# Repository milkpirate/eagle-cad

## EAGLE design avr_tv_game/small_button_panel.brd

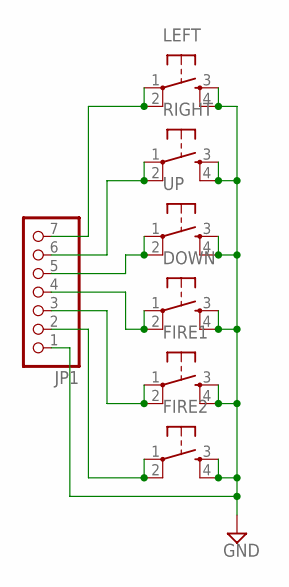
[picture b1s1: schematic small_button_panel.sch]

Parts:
DOWN: TAC_SWITCHPTH; TACTILE-PTH
FIRE1, FIRE2: TAC_SWITCHPTH; TACTILE-PTH
JP1: PINHD-1X7; 1X07
LEFT: TAC_SWITCHPTH; TACTILE-PTH
RIGHT: TAC_SWITCHPTH; TACTILE-PTH
UP: TAC_SWITCHPTH; TACTILE-PTH

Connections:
GND: DOWN.3, DOWN.4, FIRE1.3, FIRE1.4, FIRE2.3, FIRE2.4, JP1.1, LEFT.3, LEFT.4, RIGHT.3, RIGHT.4, UP.3, UP.4
unnamed: JP1.7, LEFT.1, LEFT.2
unnamed: JP1.5, UP.1, UP.2
unnamed: FIRE2.1, FIRE2.2, JP1.2
unnamed: FIRE1.1, FIRE1.2, JP1.3
unnamed: DOWN.1, DOWN.2, JP1.4
RIGHT: JP1.6, RIGHT.1, RIGHT.2

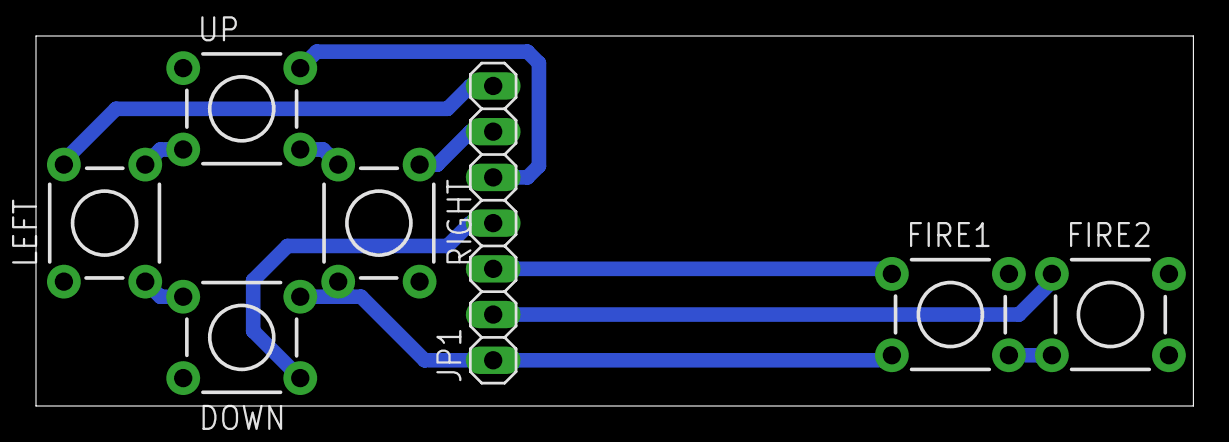
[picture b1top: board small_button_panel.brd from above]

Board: 2 copper layers, 64.3 x 20.6 mm, 7 parts (0 on the bottom side), 7 nets.

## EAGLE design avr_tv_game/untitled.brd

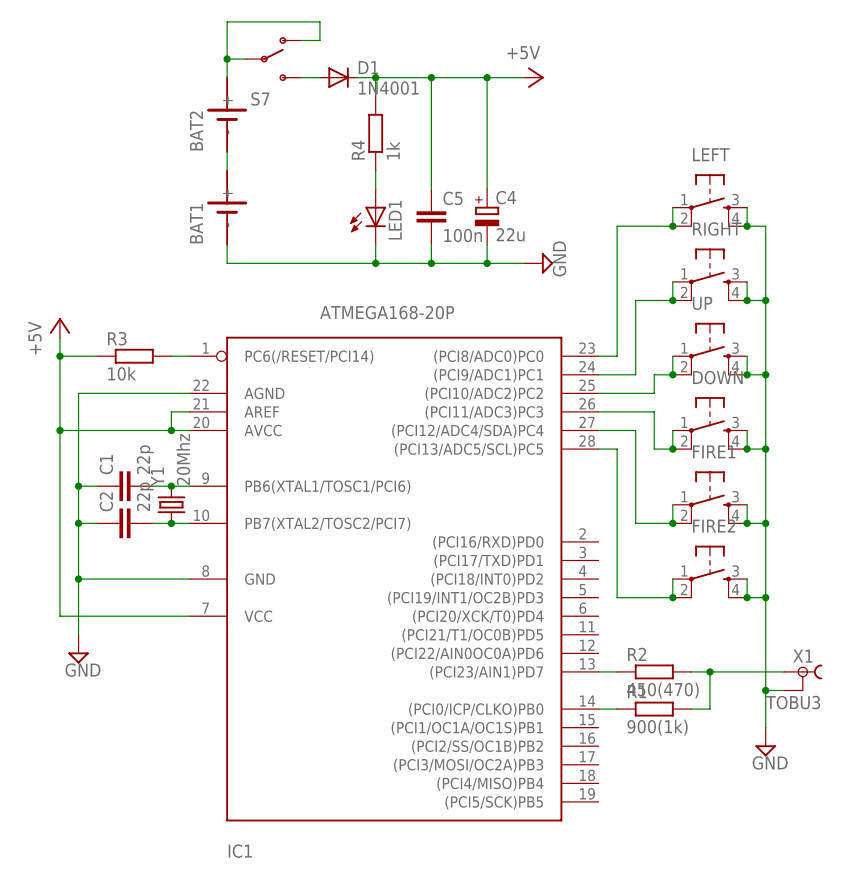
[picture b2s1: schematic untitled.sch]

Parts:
BAT1, BAT2: SN2032
C1, C2: 22p; C025-025X050
C4: 22u; TT2D5L
C5: 100n; C025-025X050
D1: 1N4001; D-2.5
DOWN: TAC_SWITCHPTH; TACTILE-PTH
FIRE1, FIRE2: TAC_SWITCHPTH; TACTILE-PTH
IC1: ATMEGA168-20P; DIL28-3
LED1: LED3MM
LEFT: TAC_SWITCHPTH; TACTILE-PTH
R1: 900(1k); 0207/2V
R2: 450(470); 0207/2V
R3: 10k; 0207/10
R4: 1k; 0204V
RIGHT: TAC_SWITCHPTH; TACTILE-PTH
S7: SWITCH-SPSTPTH; SWITCH-SPDT
UP: TAC_SWITCHPTH; TACTILE-PTH
X1: TOBU3
Y1: 20Mhz; HC49US

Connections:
+5V: C4.+, C5.1, D1.C, IC1.7 (VCC), IC1.20 (AVCC), IC1.21 (AREF), R3.1, R4.2
GND: BAT1.-, C1.1, C2.1, C4.-, C5.2, DOWN.3, DOWN.4, FIRE1.3, FIRE1.4, FIRE2.3, FIRE2.4, IC1.8 (GND), IC1.22 (AGND), LED1.K (C), LEFT.3, LEFT.4, RIGHT.3, RIGHT.4, UP.3, UP.4, X1.2, X1.2@1 (2), X1.2@2 (2)
unnamed: C1.2, IC1.9 (PB6(XTAL1/TOSC1/PCI6)), Y1.2
unnamed: C2.2, IC1.10 (PB7(XTAL2/TOSC2/PCI7)), Y1.1
unnamed: BAT2.+, S7.1 (O), S7.2
unnamed: IC1.23 ((PCI8/ADC0)PC0), LEFT.1, LEFT.2
unnamed: LED1.A, R4.1
unnamed: IC1.25 ((PCI10/ADC2)PC2), UP.1, UP.2
unnamed: IC1.1 (PC6(/RESET/PCI14)), R3.2
unnamed: FIRE2.1, FIRE2.2, IC1.28 ((PCI13/ADC5/SCL)PC5)
unnamed: FIRE1.1, FIRE1.2, IC1.27 ((PCI12/ADC4/SDA)PC4)
unnamed: DOWN.1, DOWN.2, IC1.26 ((PCI11/ADC3)PC3)
unnamed: D1.A, S7.3 (S)
unnamed: BAT1.+, BAT2.-
unnamed: IC1.14 ((PCI0/ICP/CLKO)PB0), R1.1
unnamed: IC1.13 ((PCI23/AIN1)PD7), R2.1
unnamed: R1.2, R2.2, X1.1
RIGHT: IC1.24 ((PCI9/ADC1)PC1), RIGHT.1, RIGHT.2

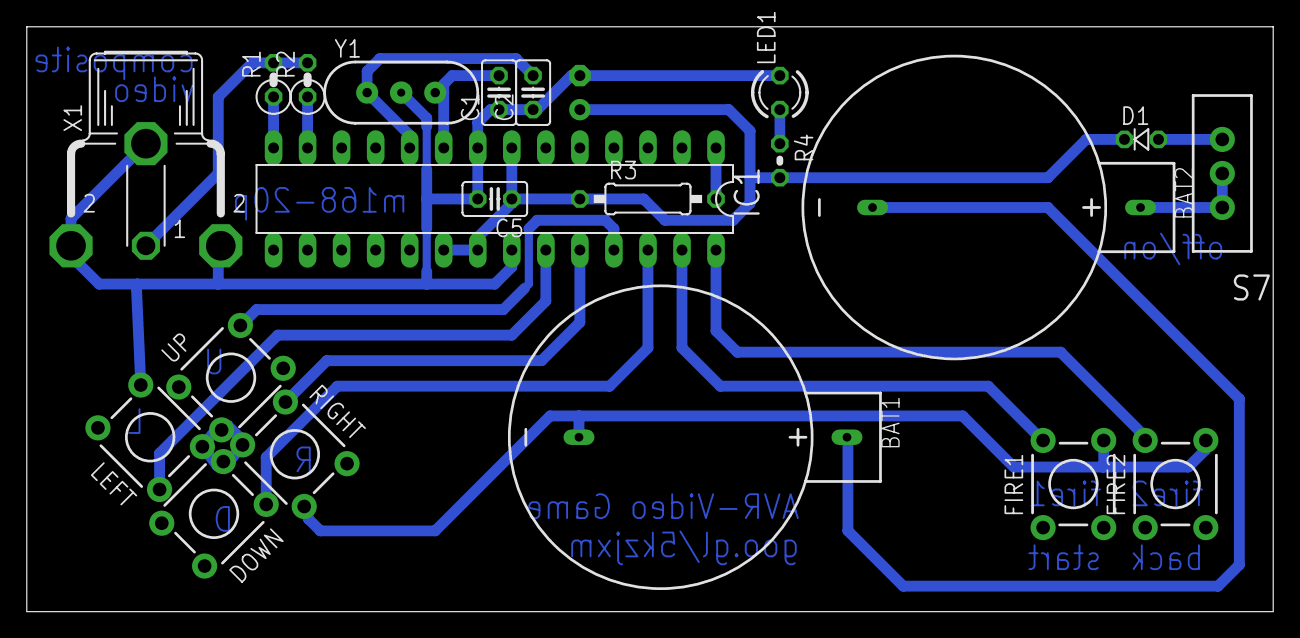
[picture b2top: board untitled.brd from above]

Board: 2 copper layers, 93.0 x 43.6 mm, 22 parts (1 on the bottom side), 18 nets.

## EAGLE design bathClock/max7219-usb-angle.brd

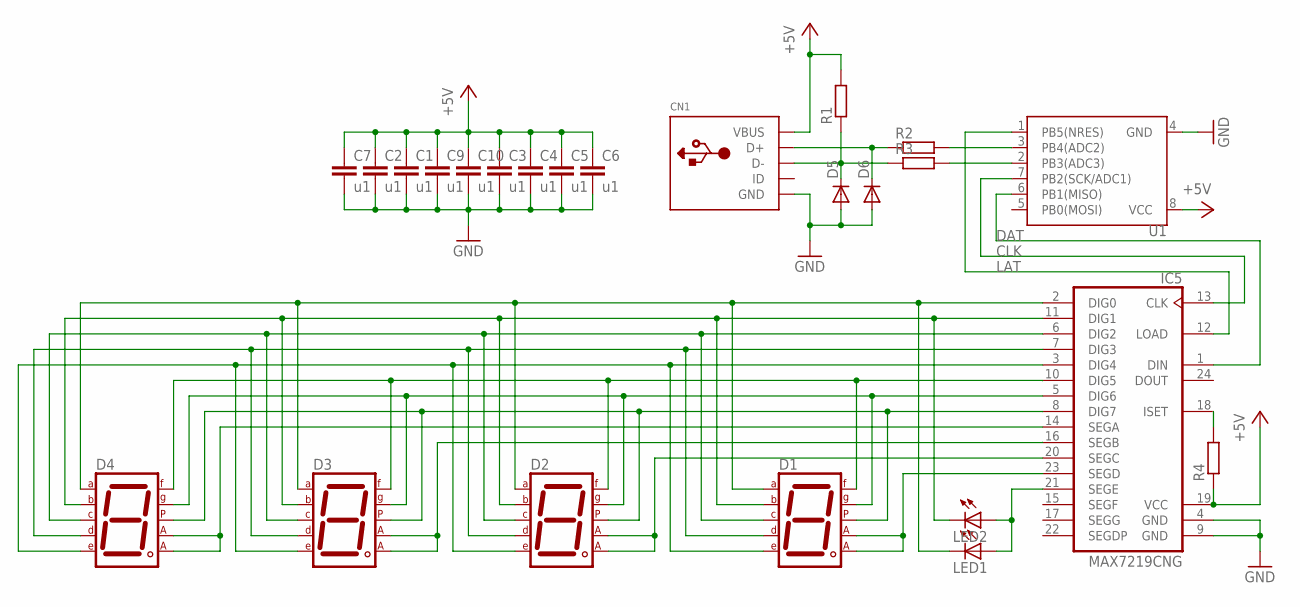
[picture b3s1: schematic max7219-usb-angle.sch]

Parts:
C1, C2, C3, C4, C5, C6, C7, C9, C10: u1; C0805K
CN1: USBTHM; USB-MINIB-THM
D1, D2, D3, D4: 7SEG-CA; 7SEG-13
D5, D6: DIODE-MINIMELF; MINIMELF
IC5: MAX7219CNG; DIL24-3
LED1, LED2: LED3MM
R1, R2, R3: R-EU_M0805; M0805
R4: R-EU_R0805; R0805
U1: ATTINY45ATTINYX5-20-DIP-GAP; DIL08

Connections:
+5V: C1.1, C2.1, C3.1, C4.1, C5.1, C6.1, C7.1, C9.1, C10.1, CN1.VBUS, IC5.19 (VCC), R1.2, R4.1, U1.8 (VCC)
CLK: IC5.13 (CLK), U1.7 (PB2(SCK/ADC1))
DAT: IC5.1 (DIN), U1.6 (PB1(MISO))
GND: C1.2, C2.2, C3.2, C4.2, C5.2, C6.2, C7.2, C9.2, C10.2, CN1.GND, D5.A, D6.A, IC5.4 (GND), IC5.9 (GND), U1.4 (GND)
LAT: IC5.12 (LOAD), U1.1 (PB5(NRES))
unnamed: D2.3 (CA1), D2.8 (CA2), IC5.20 (SEGC)
unnamed: D4.3 (CA1), D4.8 (CA2), IC5.14 (SEGA)
unnamed: D1.3 (CA1), D1.8 (CA2), IC5.23 (SEGD)
unnamed: IC5.21 (SEGE), LED1.A, LED2.A
unnamed: D1.7 (A), D2.7 (A), D3.7 (A), D4.7 (A), IC5.2 (DIG0), LED1.K (C)
unnamed: D1.6 (B), D2.6 (B), D3.6 (B), D4.6 (B), IC5.11 (DIG1), LED2.K (C)
unnamed: D1.4 (C), D2.4 (C), D3.4 (C), D4.4 (C), IC5.6 (DIG2)
unnamed: D1.2 (D), D2.2 (D), D3.2 (D), D4.2 (D), IC5.7 (DIG3)
unnamed: D1.1 (E), D2.1 (E), D3.1 (E), D4.1 (E), IC5.3 (DIG4)
unnamed: D1.9 (F), D2.9 (F), D3.9 (F), D4.9 (F), IC5.10 (DIG5)
unnamed: D1.10 (G), D2.10 (G), D3.10 (G), D4.10 (G), IC5.5 (DIG6)
unnamed: D1.5 (DP), D2.5 (DP), D3.5 (DP), D4.5 (DP), IC5.8 (DIG7)
unnamed: IC5.18 (ISET), R4.2
unnamed: D3.3 (CA1), D3.8 (CA2), IC5.16 (SEGB)
unnamed: R2.2, U1.3 (PB4(ADC2))
unnamed: CN1.D-, D5.C, R1.1, R3.1
unnamed: CN1.D+, D6.C, R2.1
unnamed: R3.2, U1.2 (PB3(ADC3))

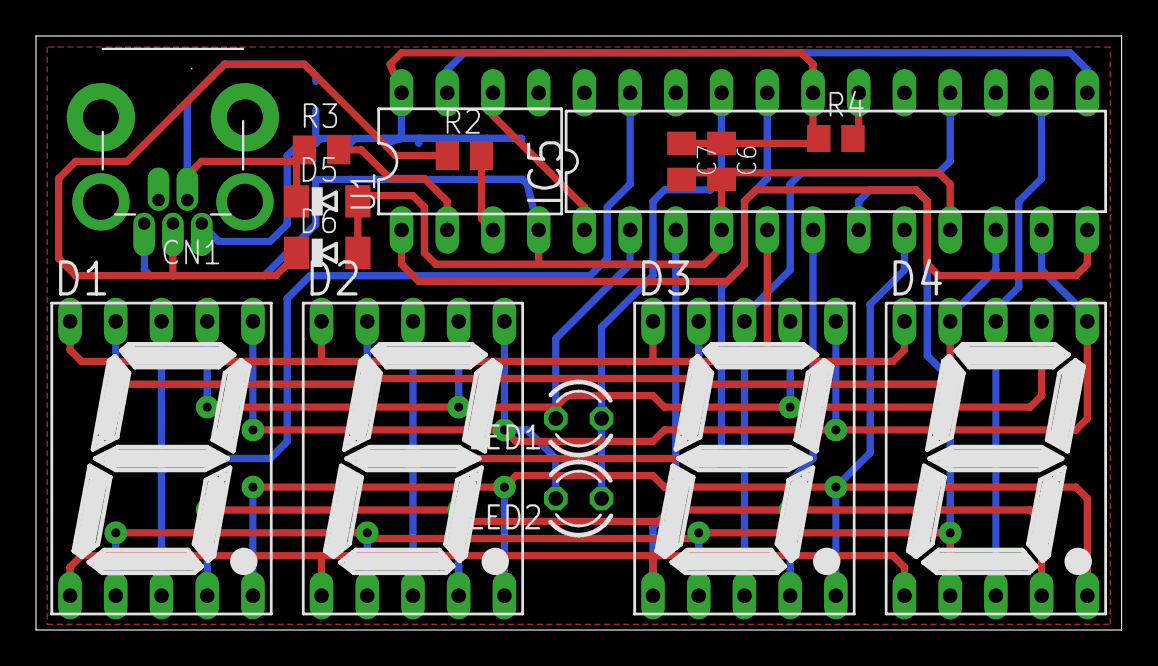
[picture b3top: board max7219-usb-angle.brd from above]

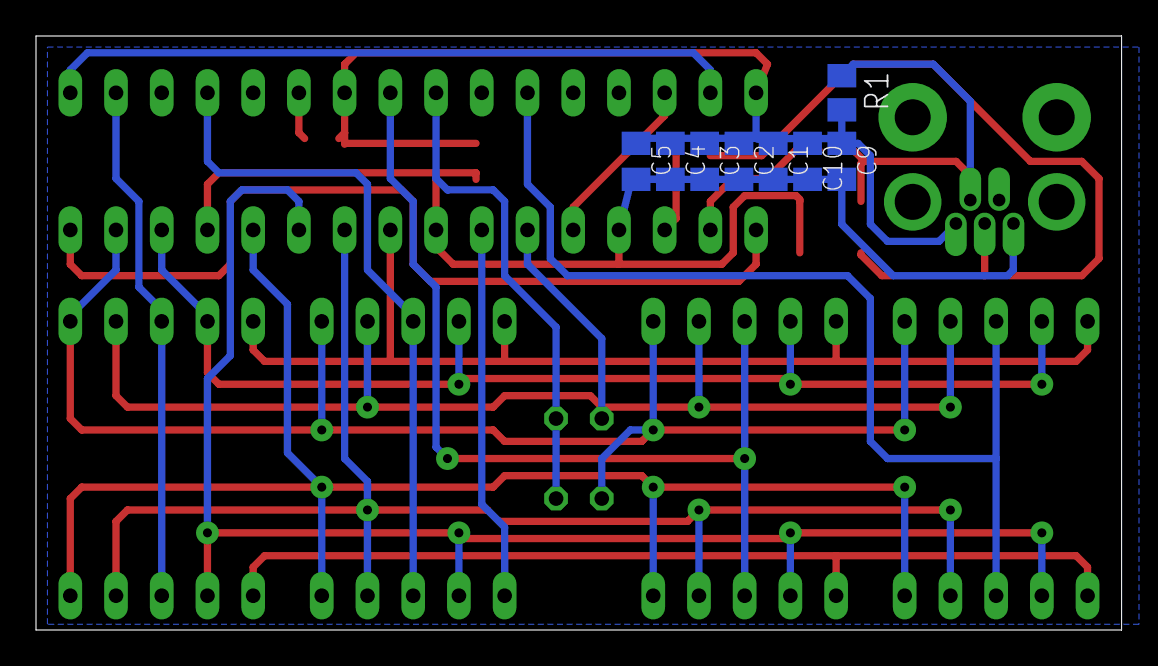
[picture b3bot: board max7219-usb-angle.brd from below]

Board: 2 copper layers, 60.3 x 33.0 mm, 24 parts (8 on the bottom side), 23 nets.

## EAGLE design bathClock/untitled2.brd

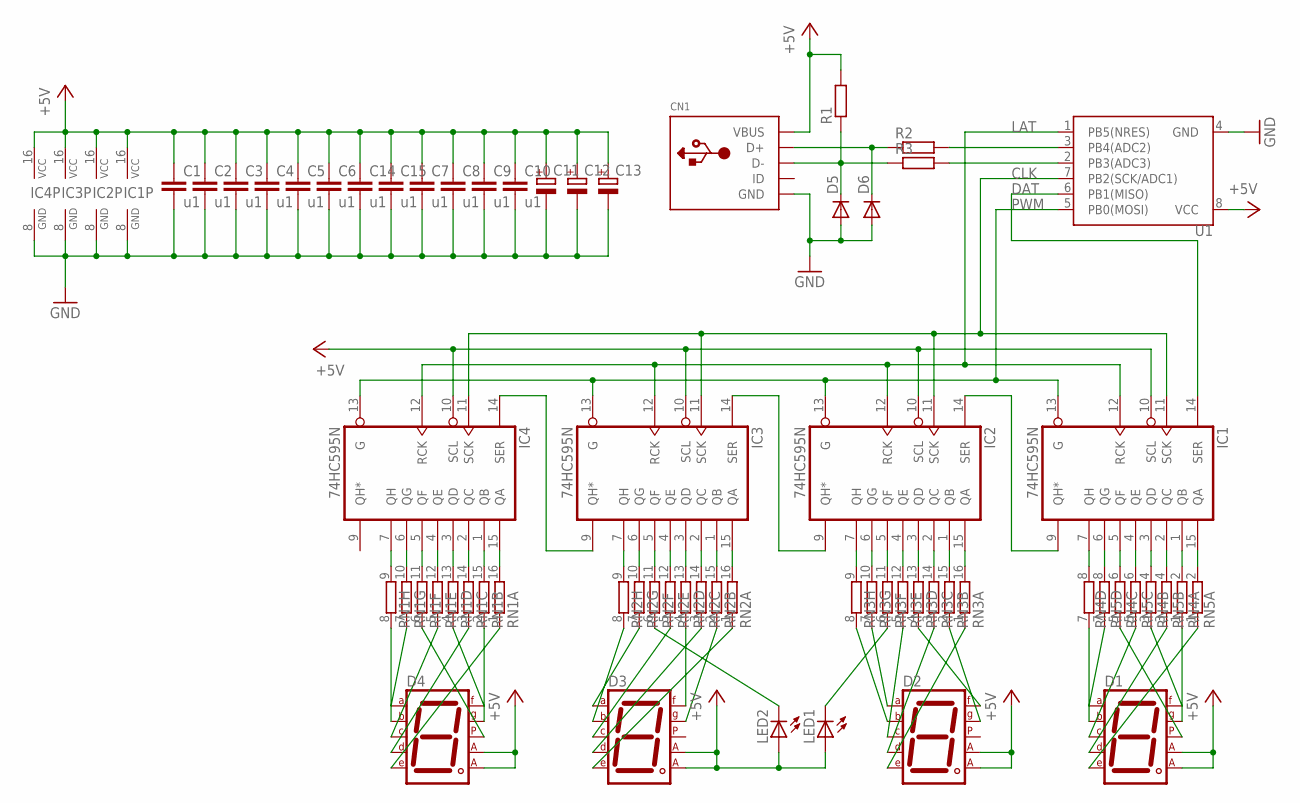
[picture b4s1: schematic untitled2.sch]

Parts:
C1, C2, C3, C4, C5, C6, C14, C15: u1; C025-025X050
C7, C8, C9, C10: u1; C0805K
C11: CPOL-EUE1.8-4; E1,8-4
C12, C13: CPOL-EUE2.5-7; E2,5-7
CN1: USBTHM; USB-MINIB-THM
D1, D2, D3, D4: 7SEG-CA; 7SEG-13
D5, D6: DIODE-D-7.5; D-7.5
IC1, IC2, IC3, IC4: 74HC595N; DIL16
LED1, LED2: LED3MM
R1, R2, R3: R-EU_0204/7; 0204/7
RN1, RN2, RN3: 8R-N; DIL16
RN4, RN5: E4R; SIL8
U1: ATTINY45ATTINYX5-20-DIP-GAP; DIL08

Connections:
+5V: C1.1, C2.1, C3.1, C4.1, C5.1, C6.1, C7.1, C8.1, C9.1, C10.1, C11.+, C12.+, C13.+, C14.1, C15.1, CN1.VBUS, D1.3 (CA1), D1.8 (CA2), D2.3 (CA1), D2.8 (CA2), D3.3 (CA1), D3.8 (CA2), D4.3 (CA1), D4.8 (CA2), IC1.10 (SCL), IC1.16 (VCC), IC2.10 (SCL), IC2.16 (VCC), IC3.10 (SCL), IC3.16 (VCC), IC4.10 (SCL), IC4.16 (VCC), LED1.A, LED2.A, R1.2, U1.8 (VCC)
CLK: IC1.11 (SCK), IC2.11 (SCK), IC3.11 (SCK), IC4.11 (SCK), U1.7 (PB2(SCK/ADC1))
DAT: IC1.14 (SER), U1.6 (PB1(MISO))
GND: C1.2, C2.2, C3.2, C4.2, C5.2, C6.2, C7.2, C8.2, C9.2, C10.2, C11.-, C12.-, C13.-, C14.2, C15.2, CN1.GND, D5.A, D6.A, IC1.8 (GND), IC2.8 (GND), IC3.8 (GND), IC4.8 (GND), U1.4 (GND)
LAT: IC1.12 (RCK), IC2.12 (RCK), IC3.12 (RCK), IC4.12 (RCK), U1.1 (PB5(NRES))
unnamed: D1.7 (A), RN5.7 (1)
unnamed: D1.6 (B), RN4.7 (1)
unnamed: D1.5 (DP), RN4.5 (1)
unnamed: D1.4 (C), RN5.5 (1)
unnamed: D1.9 (F), RN4.3 (1)
unnamed: D1.2 (D), RN5.3 (1)
unnamed: D1.10 (G), RN4.1
unnamed: D1.1 (E), RN5.1
unnamed: D4.9 (F), RN1.4 (1)
unnamed: D2.1 (E), RN3.1
unnamed: D2.2 (D), RN3.3 (1)
unnamed: D2.4 (C), RN3.5 (1)
unnamed: D2.7 (A), RN3.7 (1)
unnamed: D2.6 (B), RN3.8 (1)
unnamed: LED2.K (C), RN2.6 (1)
unnamed: D2.9 (F), RN3.4 (1)
unnamed: D2.10 (G), RN3.2 (1)
unnamed: D3.1 (E), RN2.1
unnamed: D3.2 (D), RN2.3 (1)
unnamed: D3.4 (C), RN2.5 (1)
unnamed: D3.7 (A), RN2.7 (1)
unnamed: D3.6 (B), RN2.8 (1)
unnamed: LED1.K (C), RN3.6 (1)
unnamed: D3.9 (F), RN2.4 (1)
unnamed: D3.10 (G), RN2.2 (1)
unnamed: D4.1 (E), RN1.1
unnamed: D4.2 (D), RN1.3 (1)
unnamed: D4.4 (C), RN1.5 (1)
unnamed: D4.7 (A), RN1.7 (1)
unnamed: IC1.9 (QH*), IC2.14 (SER)
unnamed: IC2.9 (QH*), IC3.14 (SER)
unnamed: IC3.9 (QH*), IC4.14 (SER)
unnamed: IC1.7 (QH), RN4.8 (2)
unnamed: IC1.15 (QA), RN5.2
unnamed: IC1.1 (QB), RN4.2
unnamed: IC1.2 (QC), RN5.4 (2)
unnamed: IC1.3 (QD), RN4.4 (2)
unnamed: IC1.4 (QE), RN5.6 (2)
unnamed: IC1.5 (QF), RN4.6 (2)
unnamed: IC1.6 (QG), RN5.8 (2)
unnamed: IC2.7 (QH), RN3.9 (2)
unnamed: IC2.15 (QA), RN3.16 (2)
unnamed: D4.6 (B), RN1.8 (1)
unnamed: D4.5 (DP), RN1.6 (1)
unnamed: D4.10 (G), RN1.2 (1)
unnamed: R2.2, U1.3 (PB4(ADC2))
unnamed: CN1.D-, D5.C, R1.1, R3.1
unnamed: CN1.D+, D6.C, R2.1
unnamed: R3.2, U1.2 (PB3(ADC3))
unnamed: IC3.15 (QA), RN2.16 (2)
unnamed: IC3.3 (QD), RN2.13 (2)
unnamed: IC3.5 (QF), RN2.11 (2)
unnamed: IC3.7 (QH), RN2.9 (2)
unnamed: IC4.7 (QH), RN1.9 (2)
unnamed: IC4.5 (QF), RN1.11 (2)
unnamed: IC4.6 (QG), RN1.10 (2)
unnamed: IC4.4 (QE), RN1.12 (2)
unnamed: IC4.3 (QD), RN1.13 (2)
unnamed: IC4.2 (QC), RN1.14 (2)
unnamed: IC4.1 (QB), RN1.15 (2)
unnamed: IC4.15 (QA), RN1.16 (2)
unnamed: IC2.1 (QB), RN3.15 (2)
unnamed: IC2.2 (QC), RN3.14 (2)
unnamed: IC2.3 (QD), RN3.13 (2)
unnamed: IC2.4 (QE), RN3.12 (2)
unnamed: IC2.5 (QF), RN3.11 (2)
unnamed: IC2.6 (QG), RN3.10 (2)
unnamed: IC3.1 (QB), RN2.15 (2)
unnamed: IC3.2 (QC), RN2.14 (2)
unnamed: IC3.4 (QE), RN2.12 (2)
unnamed: IC3.6 (QG), RN2.10 (2)
PWM: IC1.13 (G), IC2.13 (G), IC3.13 (G), IC4.13 (G), U1.5 (PB0(MOSI))

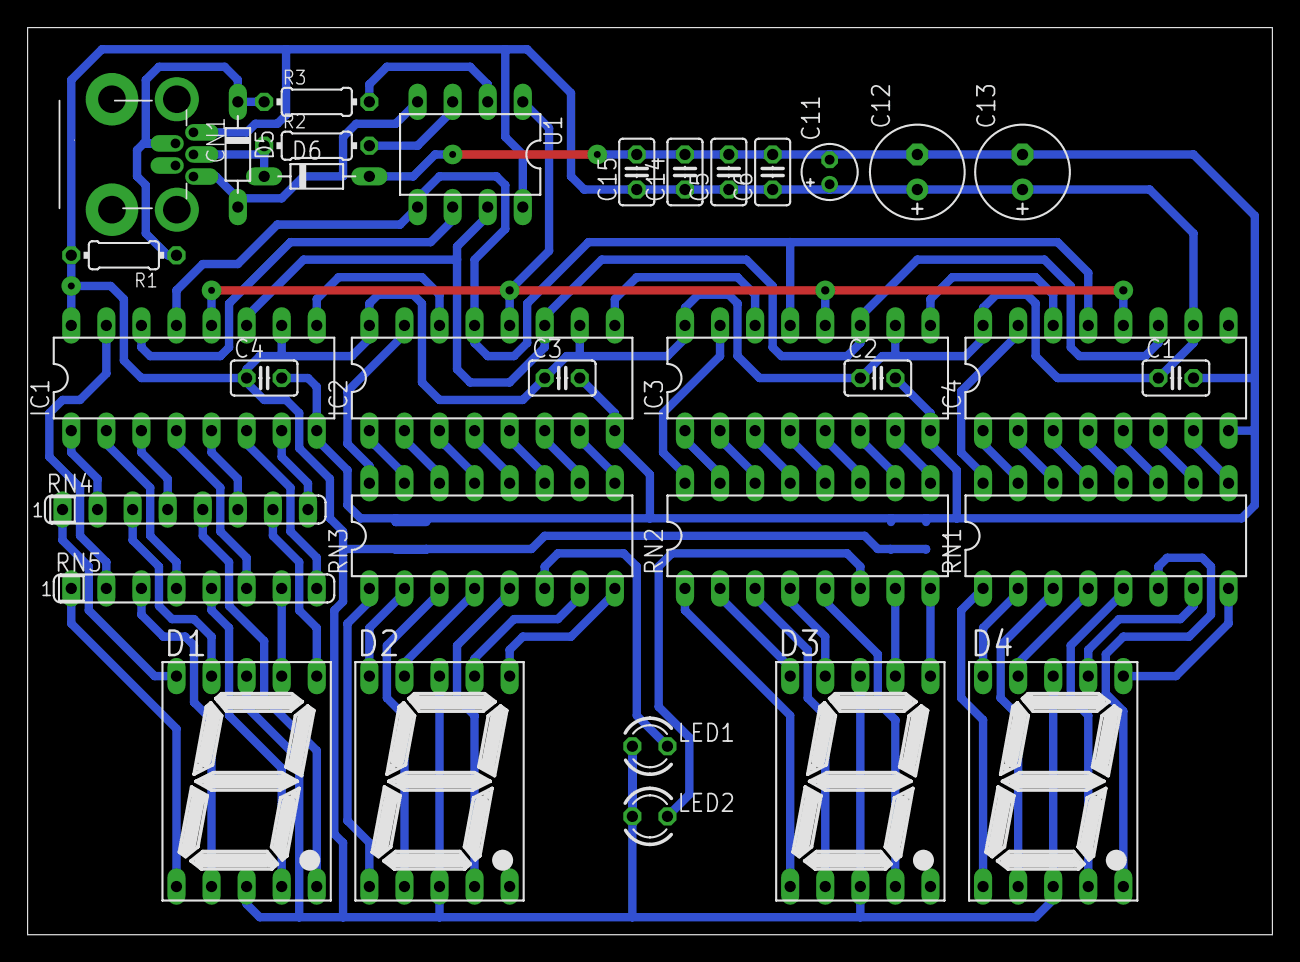
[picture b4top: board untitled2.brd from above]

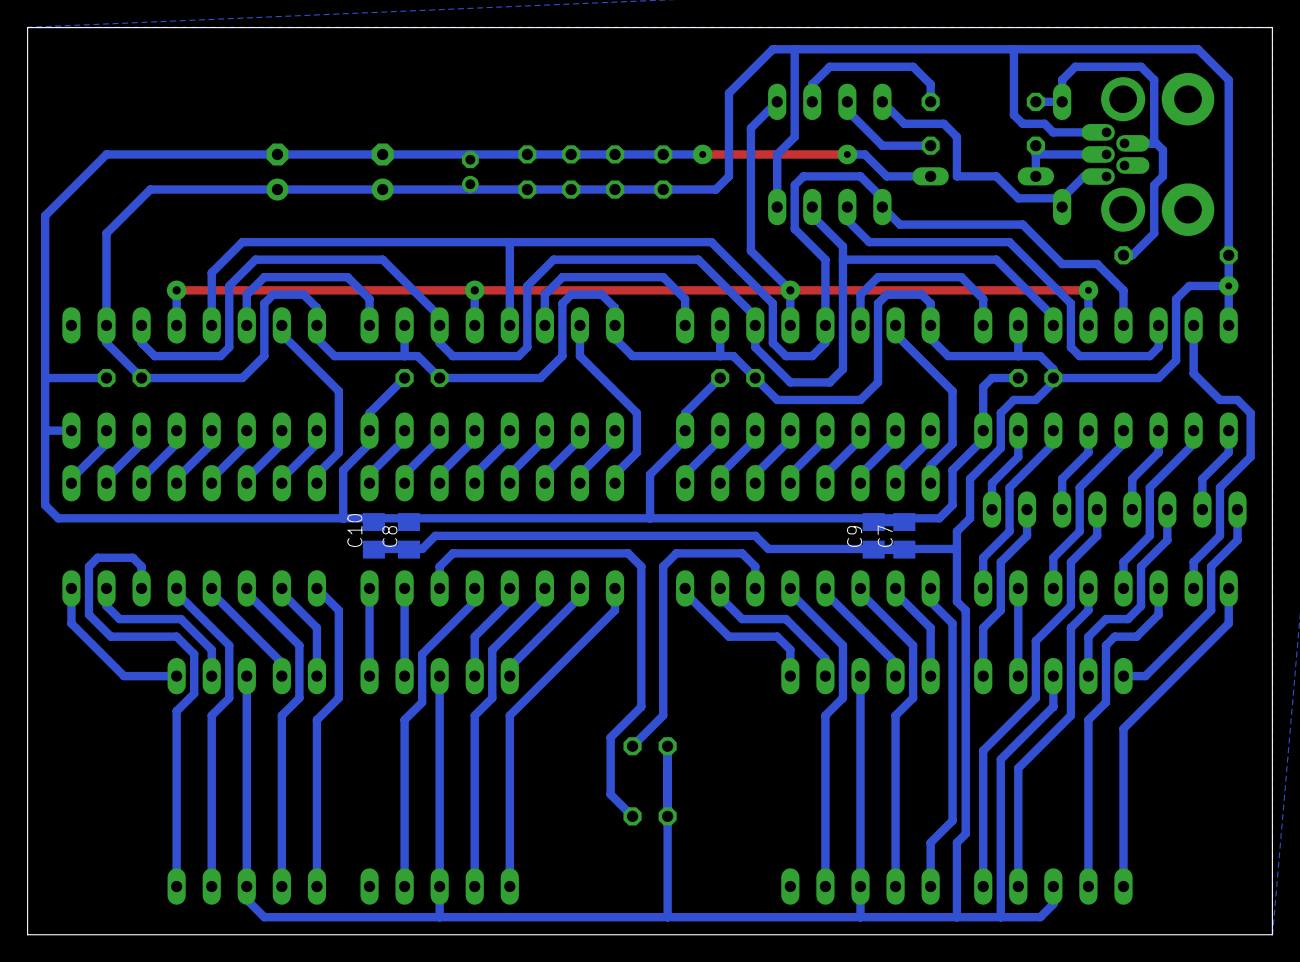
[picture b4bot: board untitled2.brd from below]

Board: 2 copper layers, 90.2 x 65.7 mm, 37 parts (4 on the bottom side), 77 nets.

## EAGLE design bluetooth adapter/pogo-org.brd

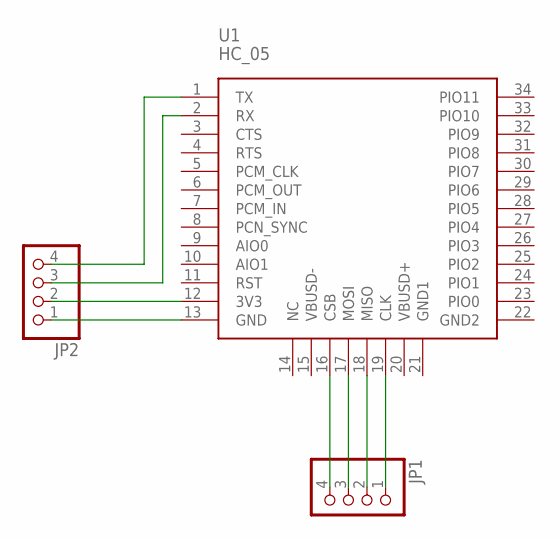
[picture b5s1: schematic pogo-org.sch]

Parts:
JP1, JP2: PINHD-1X4; 1X04
U1: HC_05; BLUETOOTH_SMD

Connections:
unnamed: JP1.1, U1.19 (CLK)
unnamed: JP1.2, U1.18 (MISO)
unnamed: JP1.3, U1.17 (MOSI)
unnamed: JP1.4, U1.16 (CSB)
unnamed: JP2.1, U1.13 (GND)
unnamed: JP2.2, U1.12 (3V3)
unnamed: JP2.3, U1.2 (RX)
unnamed: JP2.4, U1.1 (TX)

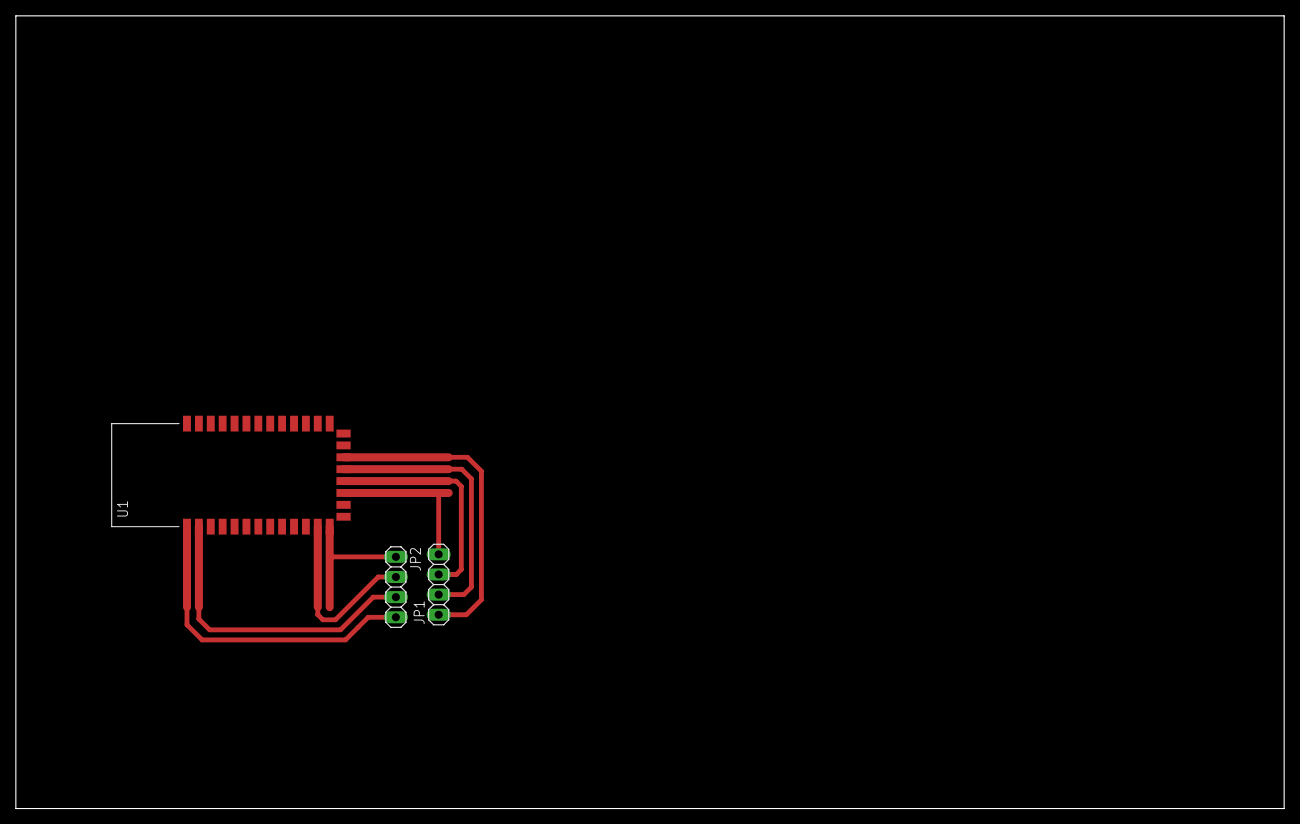
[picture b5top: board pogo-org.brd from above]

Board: 2 copper layers, 160.0 x 100.0 mm, 3 parts (0 on the bottom side), 8 nets.

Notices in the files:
parts and their libraries:
SparkFun-Electromechanical: Licensing: CC v3.0 Share-Alike You are welcome to use this library for commercial purposes.
